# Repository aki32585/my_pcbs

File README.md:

### 個人的に制作した基板の置き場
#### MITライセンスです
テスト
rere_test

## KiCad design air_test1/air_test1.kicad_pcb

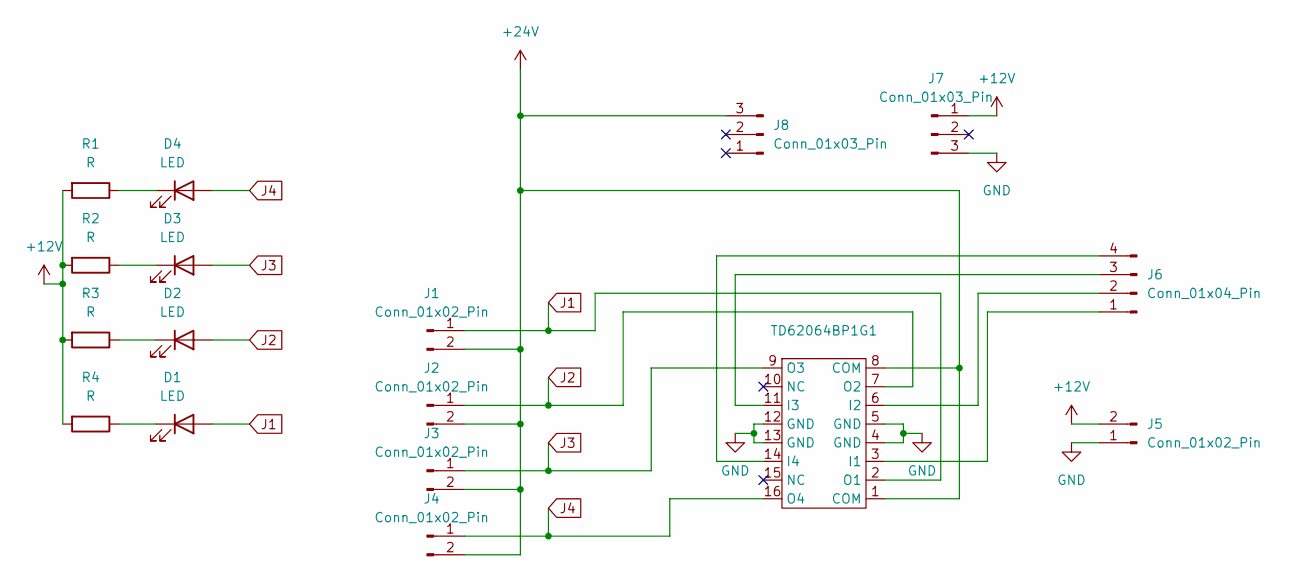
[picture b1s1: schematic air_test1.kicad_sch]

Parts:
D1, D2, D3, D4: LED; LED_D5.0mm
J1, J2, J3, J4, J5: Conn_01x02_Pin; JST_XH_S2B-XH-A-1_1x02_P2.50mm_Horizontal
J6: Conn_01x04_Pin; JST_XH_S4B-XH-A-1_1x04_P2.50mm_Horizontal
J7, J8: Conn_01x03_Pin; PinHeader_1x03_P2.54mm_Vertical
R1, R2, R3, R4: R; R_Axial_DIN0207_L6.3mm_D2.5mm_P7.62mm_Horizontal
TD62064BP1G1: DIP-16_W7.62mm_Socket

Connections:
+12V: J5.2, J7.1, R1.2, R2.2, R3.2, R4.2
+24V: J1.2, J2.2, J3.2, J4.2, J8.3, TD62064BP1G1.1 (COM), TD62064BP1G1.8 (COM)
GND: J5.1, J7.3, TD62064BP1G1.4 (GND), TD62064BP1G1.5 (GND), TD62064BP1G1.12 (GND), TD62064BP1G1.13 (GND)
J1: D1.2 (A), J1.1, TD62064BP1G1.2 (O1)
J2: D2.2 (A), J2.1, TD62064BP1G1.7 (O2)
J3: D3.2 (A), J3.1, TD62064BP1G1.9 (O3)
J4: D4.2 (A), J4.1, TD62064BP1G1.16 (O4)
unnamed: D1.1 (K), R4.1
unnamed: D2.1 (K), R3.1
unnamed: D3.1 (K), R2.1
unnamed: D4.1 (K), R1.1
unnamed: J6.1, TD62064BP1G1.3 (I1)
unnamed: J6.2, TD62064BP1G1.6 (I2)
unnamed: J6.3, TD62064BP1G1.11 (I3)
unnamed: J6.4, TD62064BP1G1.14 (I4)

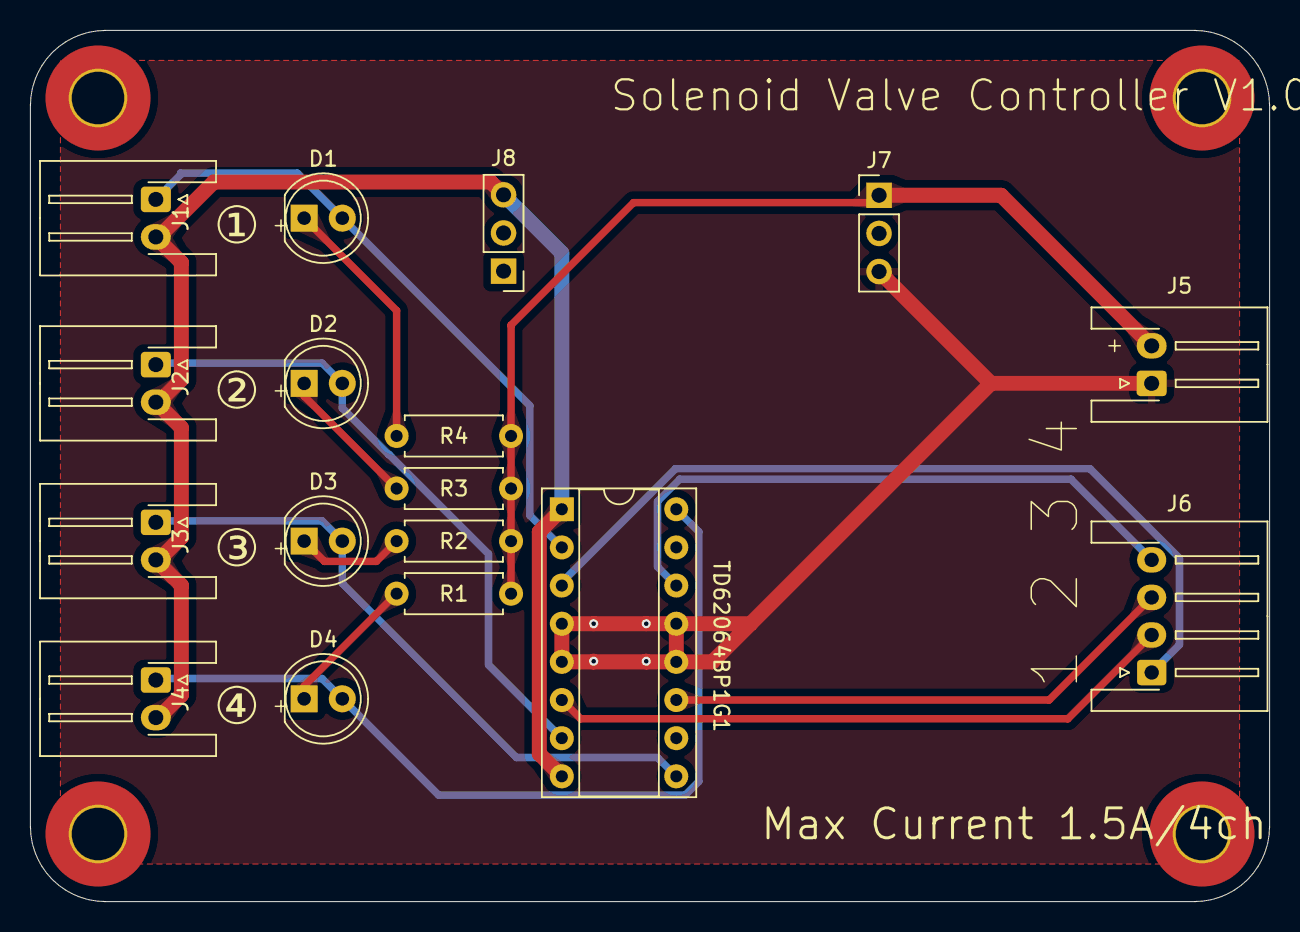
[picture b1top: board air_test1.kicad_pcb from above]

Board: 2 copper layers, 82.5 x 58.0 mm, 17 parts (0 on the bottom side), 15 nets.

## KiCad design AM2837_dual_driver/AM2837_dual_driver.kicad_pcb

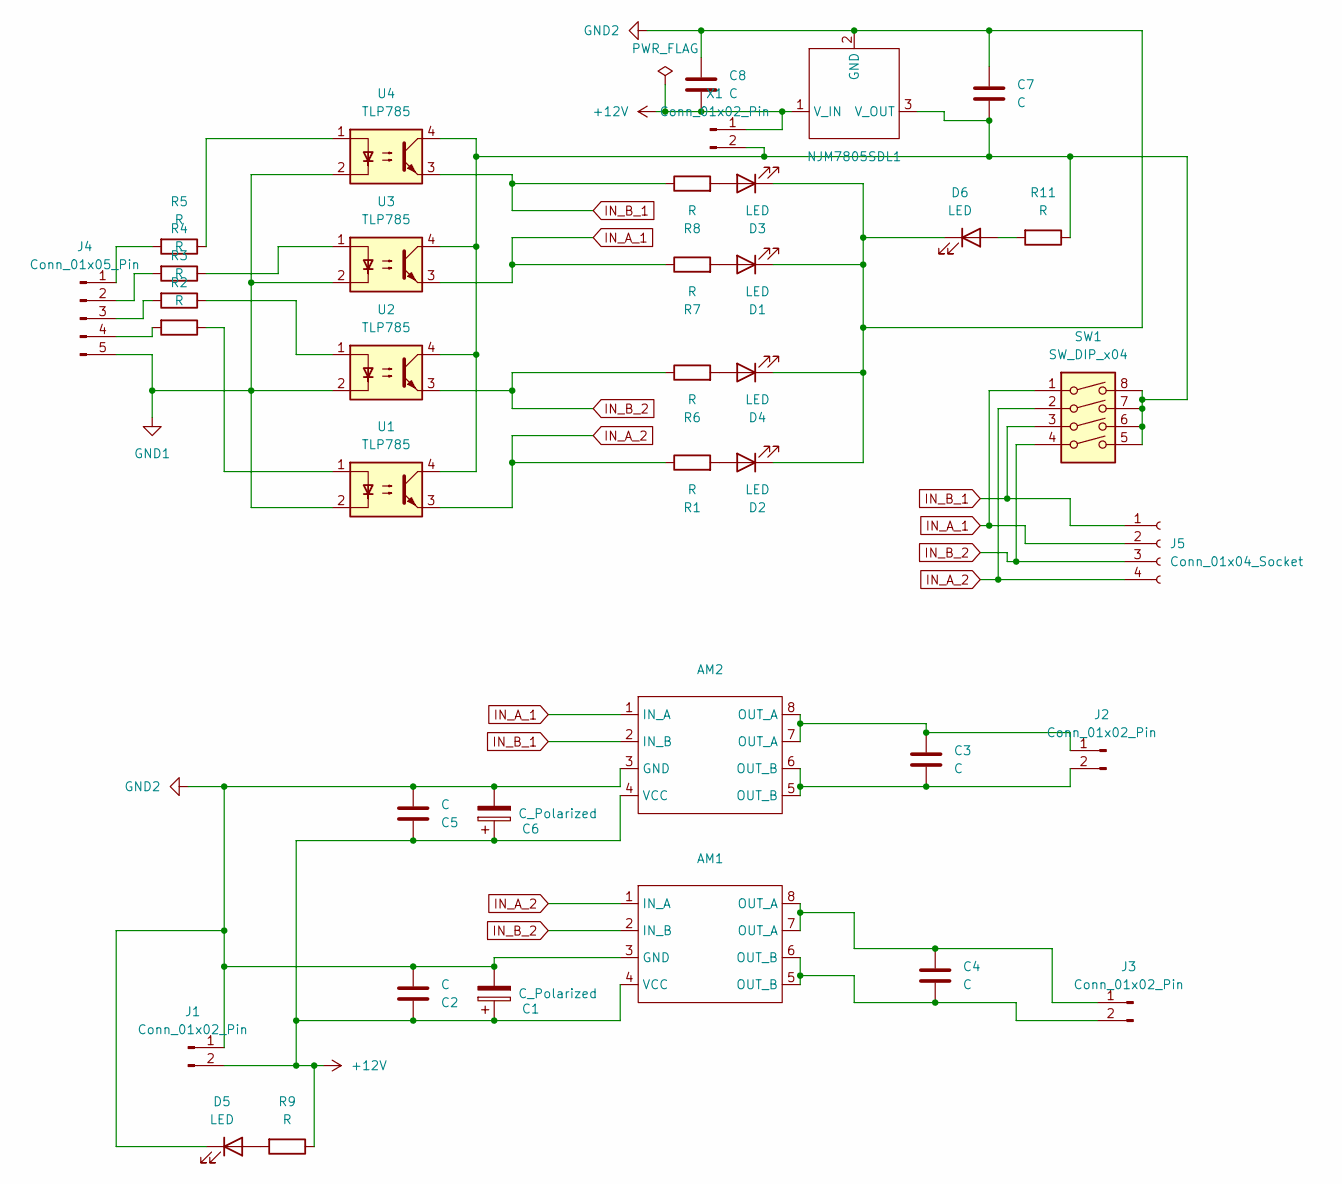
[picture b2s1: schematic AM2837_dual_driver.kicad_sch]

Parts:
AM1, AM2: SOP-8_3.76x4.96mm_P1.27mm
C1, C6: C_Polarized; CP_Radial_D8.0mm_P3.50mm
C2, C3, C4, C5: C; C_0603_1608Metric
C7, C8: C; C_0603_1608Metric_Pad1.08x0.95mm_HandSolder
D1, D2, D3, D4, D5, D6: LED; LED_0603_1608Metric_Pad1.05x0.95mm_HandSolder
J1, J2, J3: Conn_01x02_Pin; JST_VH_B2P-VH_1x02_P3.96mm_Vertical
J4: Conn_01x05_Pin; JST_XH_B5B-XH-AM_1x05_P2.50mm_Vertical
J5: Conn_01x04_Socket; JST_XH_B4B-XH-A_1x04_P2.50mm_Vertical
NJM7805SDL1: TO-252-3_TabPin2
R1, R2, R3, R4, R5, R6, R7, R8, R9, R11: R; R_0603_1608Metric_Pad0.98x0.95mm_HandSolder
SW1: SW_DIP_x04; DIP-8_W7.62mm_Socket
U1, U2, U3, U4: TLP785; DIP-4_W7.62mm
X1: Conn_01x02_Pin; C_0603_1608Metric_Pad1.08x0.95mm_HandSolder

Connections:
+12V: AM1.4 (VCC), AM2.4 (VCC), C1.1, C2.1, C5.1, C6.1, C8.2, J1.2, NJM7805SDL1.1 (V_IN), R9.1, X1.1
GND1: J4.5, U1.2, U2.2, U3.2, U4.2
GND2: AM1.3 (GND), AM2.3 (GND), C1.2, C2.2, C5.2, C6.2, C7.1, C8.1, D1.1 (K), D2.1 (K), D3.1 (K), D4.1 (K), D5.1 (K), D6.1 (K), J1.1, NJM7805SDL1.2 (GND)
IN_A_1: AM2.1 (IN_A), J5.2, R7.1, SW1.1, U3.3
IN_A_2: AM1.1 (IN_A), J5.4, R1.1, SW1.2, U1.3
IN_B_1: AM2.2 (IN_B), J5.1, R8.1, SW1.3, U4.3
IN_B_2: AM1.2 (IN_B), J5.3, R6.1, SW1.4, U2.3
unnamed: D1.2 (A), R7.2
unnamed: D2.2 (A), R1.2
unnamed: D3.2 (A), R8.2
unnamed: D4.2 (A), R6.2
unnamed: D5.2 (A), R9.2
unnamed: D6.2 (A), R11.2
unnamed: AM2.7 (OUT_A), AM2.8 (OUT_A), C3.1, J2.1
unnamed: AM2.5 (OUT_B), AM2.6 (OUT_B), C3.2, J2.2
unnamed: AM1.7 (OUT_A), AM1.8 (OUT_A), C4.1, J3.1
unnamed: AM1.5 (OUT_B), AM1.6 (OUT_B), C4.2, J3.2
unnamed: J4.1, R5.2
unnamed: J4.2, R4.2
unnamed: J4.3, R3.2
unnamed: J4.4, R2.2
unnamed: C7.2, NJM7805SDL1.3 (V_OUT), R11.1, SW1.5, SW1.6, SW1.7, SW1.8, U1.4, U2.4, U3.4, U4.4, X1.2
unnamed: R2.1, U1.1
unnamed: R3.1, U2.1
unnamed: R4.1, U3.1
unnamed: R5.1, U4.1

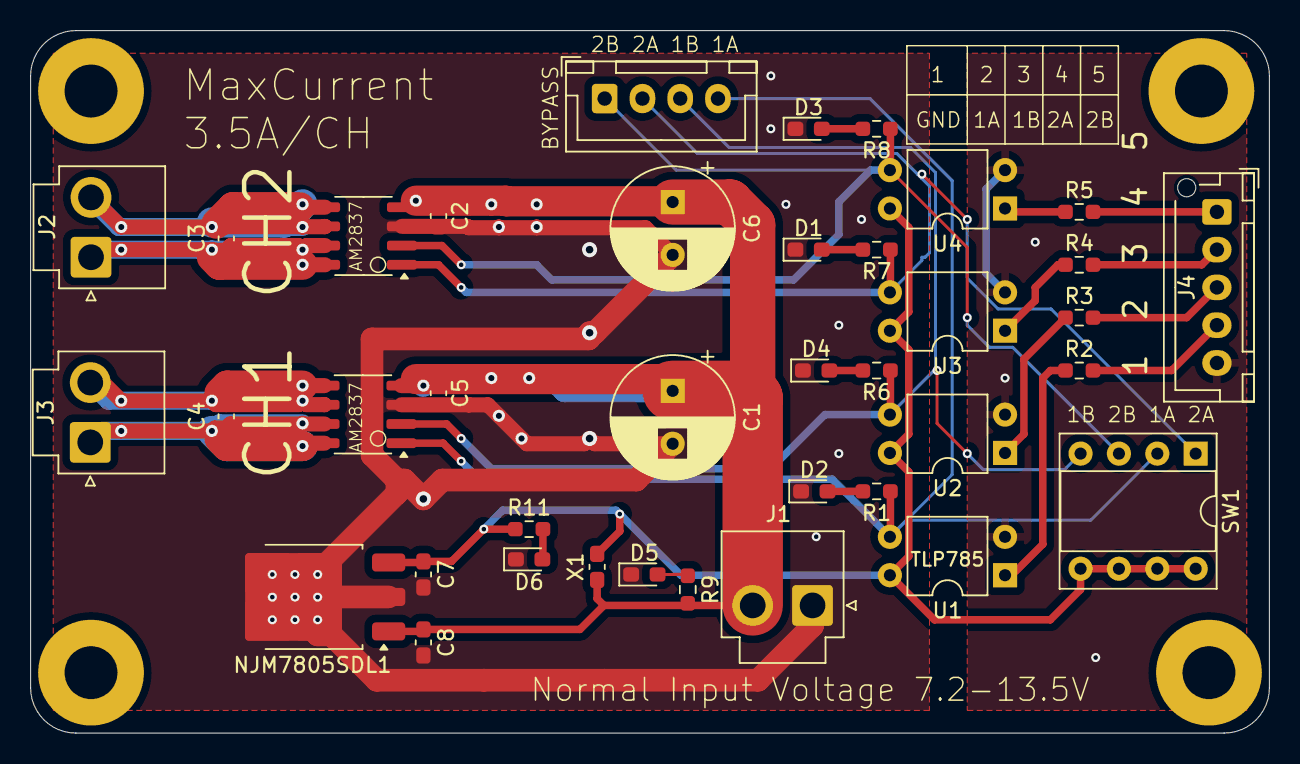
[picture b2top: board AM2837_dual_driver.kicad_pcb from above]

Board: 2 copper layers, 82.0 x 46.5 mm, 38 parts (0 on the bottom side), 26 nets.

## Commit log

2024-10-02 add air_pcb
2024-10-03 update some data and add garber
2024-10-06 Create LICENSE
2024-11-07 upload new project
2025-06-11 Update README.md 2
2025-06-11 Redmeをアップデート
